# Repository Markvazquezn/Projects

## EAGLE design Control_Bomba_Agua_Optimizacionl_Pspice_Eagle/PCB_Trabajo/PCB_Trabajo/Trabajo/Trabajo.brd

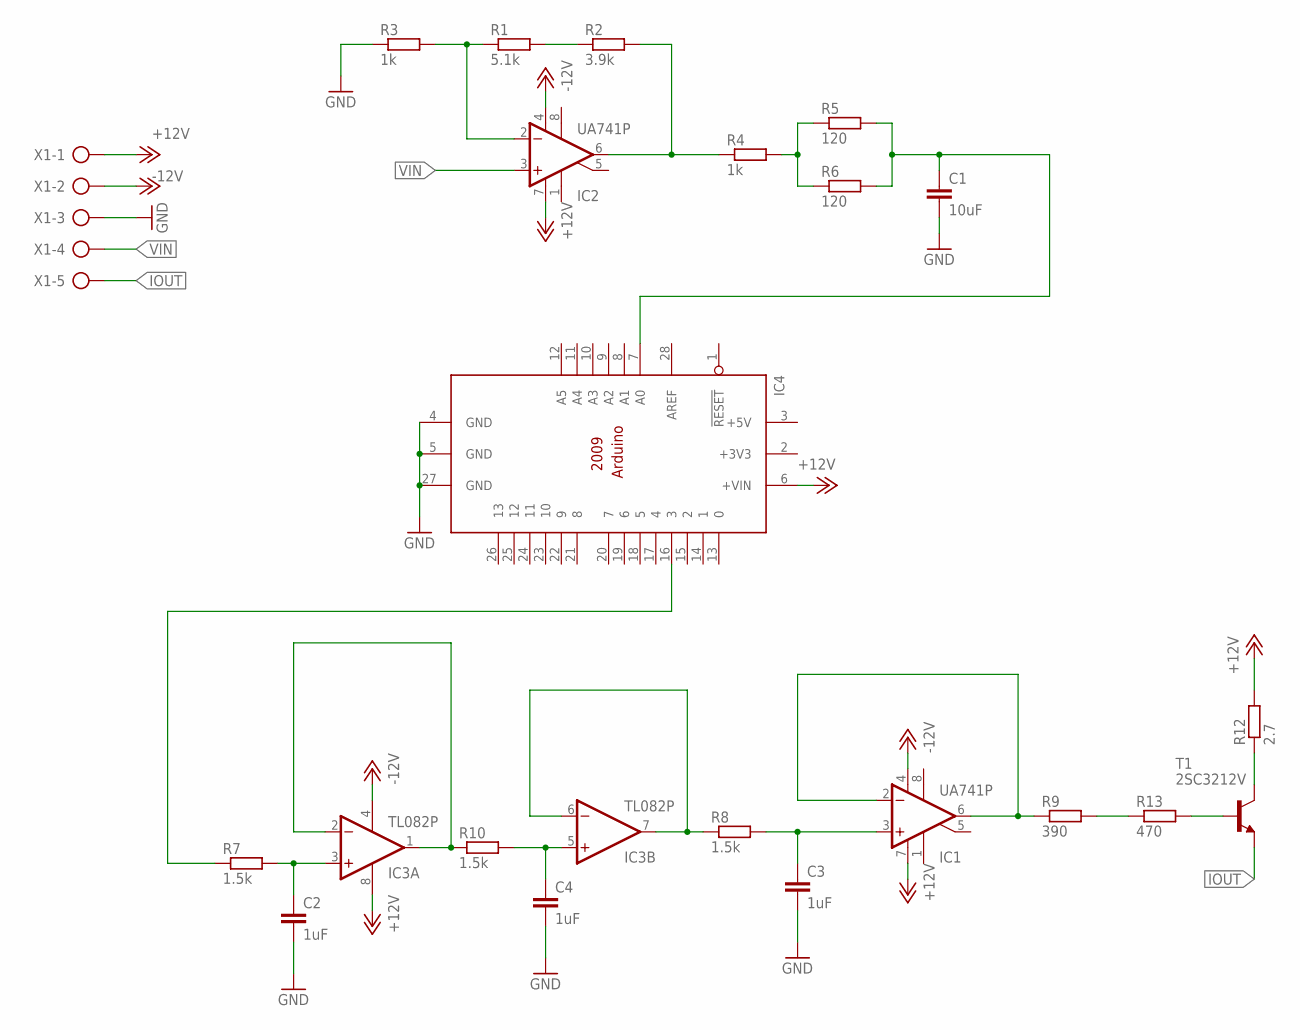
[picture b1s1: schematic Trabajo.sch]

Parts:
C1: 10uF; C025-024X044
C2, C3, C4: 1uF; C025-024X044
IC1, IC2: UA741P; DIL08
IC3: TL082P; DIL08
IC4: ARDUINO2009_10; ARDUINO2009
R1: 5.1k; 0204/7
R2: 3.9k; 0204/7
R3, R4: 1k; 0204/7
R5, R6: 120; 0204/7
R7, R8, R10: 1.5k; 0204/7
R9: 390; 0204/7
R12: 2.7; 0204/7
R13: 470; 0204/7
T1: 2SC3212V; TO220AV
X1: AK300/5

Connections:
+3V3: IC4.2 (+3V3)
+5V: IC4.3 (+5V)
+12V: IC1.7 (V+), IC2.7 (V+), IC3.8 (V+), IC4.6 (+VIN), R12.2, X1.1
-12V: IC1.4 (V-), IC2.4 (V-), IC3.4 (V-), X1.2
GND: C1.2, C2.2, C3.2, C4.2, IC4.4 (GND), IC4.5 (GND), IC4.27 (GND), R3.1, X1.3
IOUT: T1.3 (E), X1.5
unnamed: IC2.2 (-IN), R1.1, R3.2
unnamed: R4.2, R5.1, R6.1
unnamed: R1.2, R2.1
unnamed: IC2.6 (OUT), R2.2, R4.1
unnamed: IC3.1 (OUT), IC3.2 (-IN), R10.1
unnamed: C2.1, IC3.3 (+IN), R7.2
unnamed: C4.1, IC3.5 (+IN), R10.2
unnamed: IC3.6 (-IN), IC3.7 (OUT), R8.1
unnamed: C3.1, IC1.3 (+IN), R8.2
unnamed: IC1.2 (-IN), IC1.6 (OUT), R9.1
unnamed: R12.1, T1.2 (C)
unnamed: R13.2, T1.1 (B)
unnamed: R9.2, R13.1
VIN: IC2.3 (+IN), X1.4
VIN2: IC4.16 (3), R7.1
VOUT: C1.1, IC4.7 (A0), R5.2, R6.2

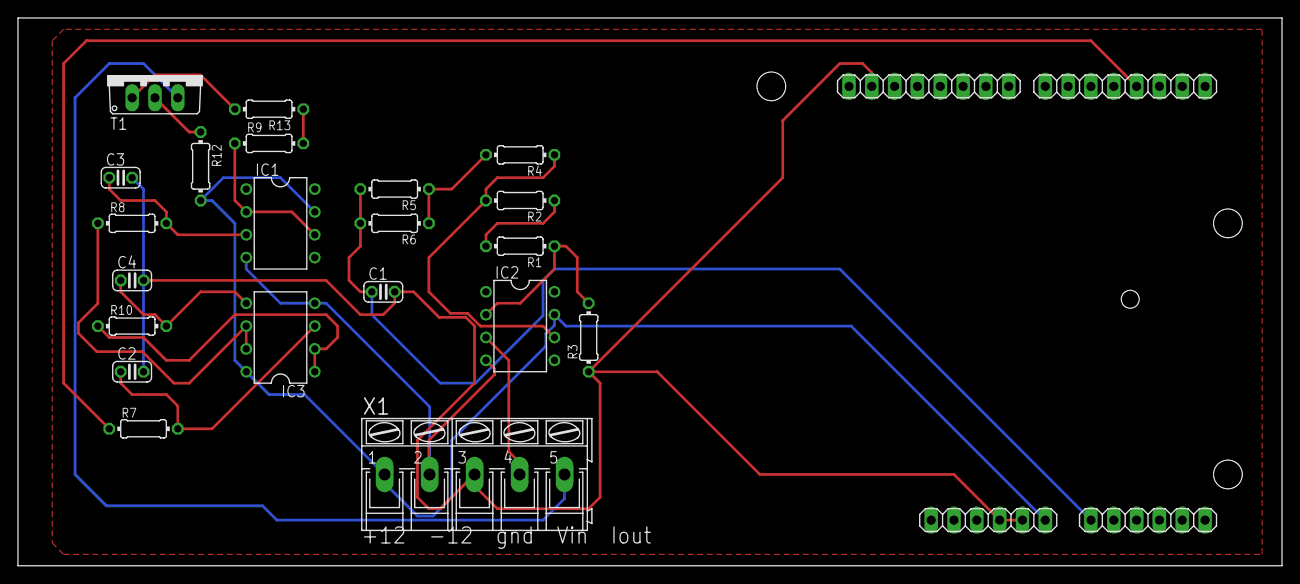
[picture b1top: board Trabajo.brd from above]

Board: 2 copper layers, 140.6 x 61.0 mm, 22 parts (0 on the bottom side), 20 nets.

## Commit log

2021-06-16 Se agrega el proyecto Coband
2021-06-16 Se agrega el proyecto SmartBand
2021-06-16 Cambios
